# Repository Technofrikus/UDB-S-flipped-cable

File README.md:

# UDB-S-flipped-cable
Version of the Unified Daugher Board S1 with ezMate connector,
but with flipped pins to use off-the-shelf ezMate-cables. Where Pin1 on the one side is connected to Pin4 on the other end.

Cable available here for example:
https://www.distrelec.de/en/cable-assembly-2mm-pitch-pico-ezmate-receptacle-pico-ezmate-receptacle-circuits-150mm-black-molex-36920-0402/p/30156720

## Pictures
y

## For more infos, please visit
https://unified-daughterboard.github.io/

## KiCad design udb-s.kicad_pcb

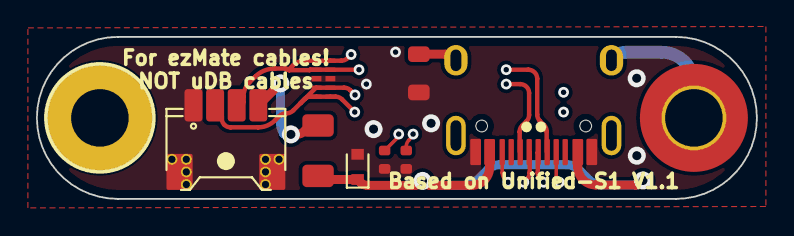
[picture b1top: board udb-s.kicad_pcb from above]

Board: 4 copper layers, 40.0 x 9.0 mm, 10 parts (0 on the bottom side), 8 nets.

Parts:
D1: ESD5Z5V0; D_SOD-523
F1: SMD0805-050-16V; Fuse_1206_3216Metric
FB1: GZ2012D601TF; L_0805_2012Metric
H1: MountingHole; MountingHole_3.2mm_M3_DIN965_Pad_TopBottom
H2: MountingHole; MountingHole_3.2mm_M3_DIN965_Pad_TopOnly
J1: TYPE-C-31-M-12; HRO-TYPE-C-31-M-12-Assembly
J2: 78171-0004; PicoEZMate-Reinforced-Lite
R1, R2: 5.1k; R_0402_1005Metric
U1: TPD4E05U06DQAR; USON-10_2.5x1.0mm_P0.5mm

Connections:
5V: F1.2, J2.4
D+: J1.A6 (D+), J1.B6 (D+), J2.2, U1.4 (D2+), U1.5 (D2-), U1.6 (NC), U1.7 (NC)
D-: J1.A7 (D-), J1.B7 (D-), J2.3, U1.1 (IO1), U1.2 (IO2), U1.9 (NC), U1.10 (NC)
GND: D1.2 (A2), FB1.2, J1.A1 (GND), J1.B1 (GND), J2.1, J2.MP (MountPin), R1.1, R2.2, U1.3 (GND), U1.8 (GND)
GNDPWR: FB1.1, H1.1, J1.S1 (SHIELD)
unnamed: J1.A5 (CC1), R1.2
unnamed: J1.B5 (CC2), R2.1
VBUS: D1.1 (A1), F1.1, J1.A4 (VBUS), J1.B4 (VBUS)

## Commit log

2023-11-11 Changed the Pinout of the ezMate connector. Added panelization with KiKit. 2x5 panels is about as small as possible for PCBA at JLCPCB, they want 70x70mm minimal size of the PCB. This means 50 PCBs i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
2023-11-11 Updated 3D models Added Renders
2023-11-11 Added Renders
2023-11-11 Changed link to correct one with 4 pins, not 3
2023-11-24 Added Panelized Version
2024-03-15 Update README.md
    Corrected link to cable with 4 circuits instead of 3
